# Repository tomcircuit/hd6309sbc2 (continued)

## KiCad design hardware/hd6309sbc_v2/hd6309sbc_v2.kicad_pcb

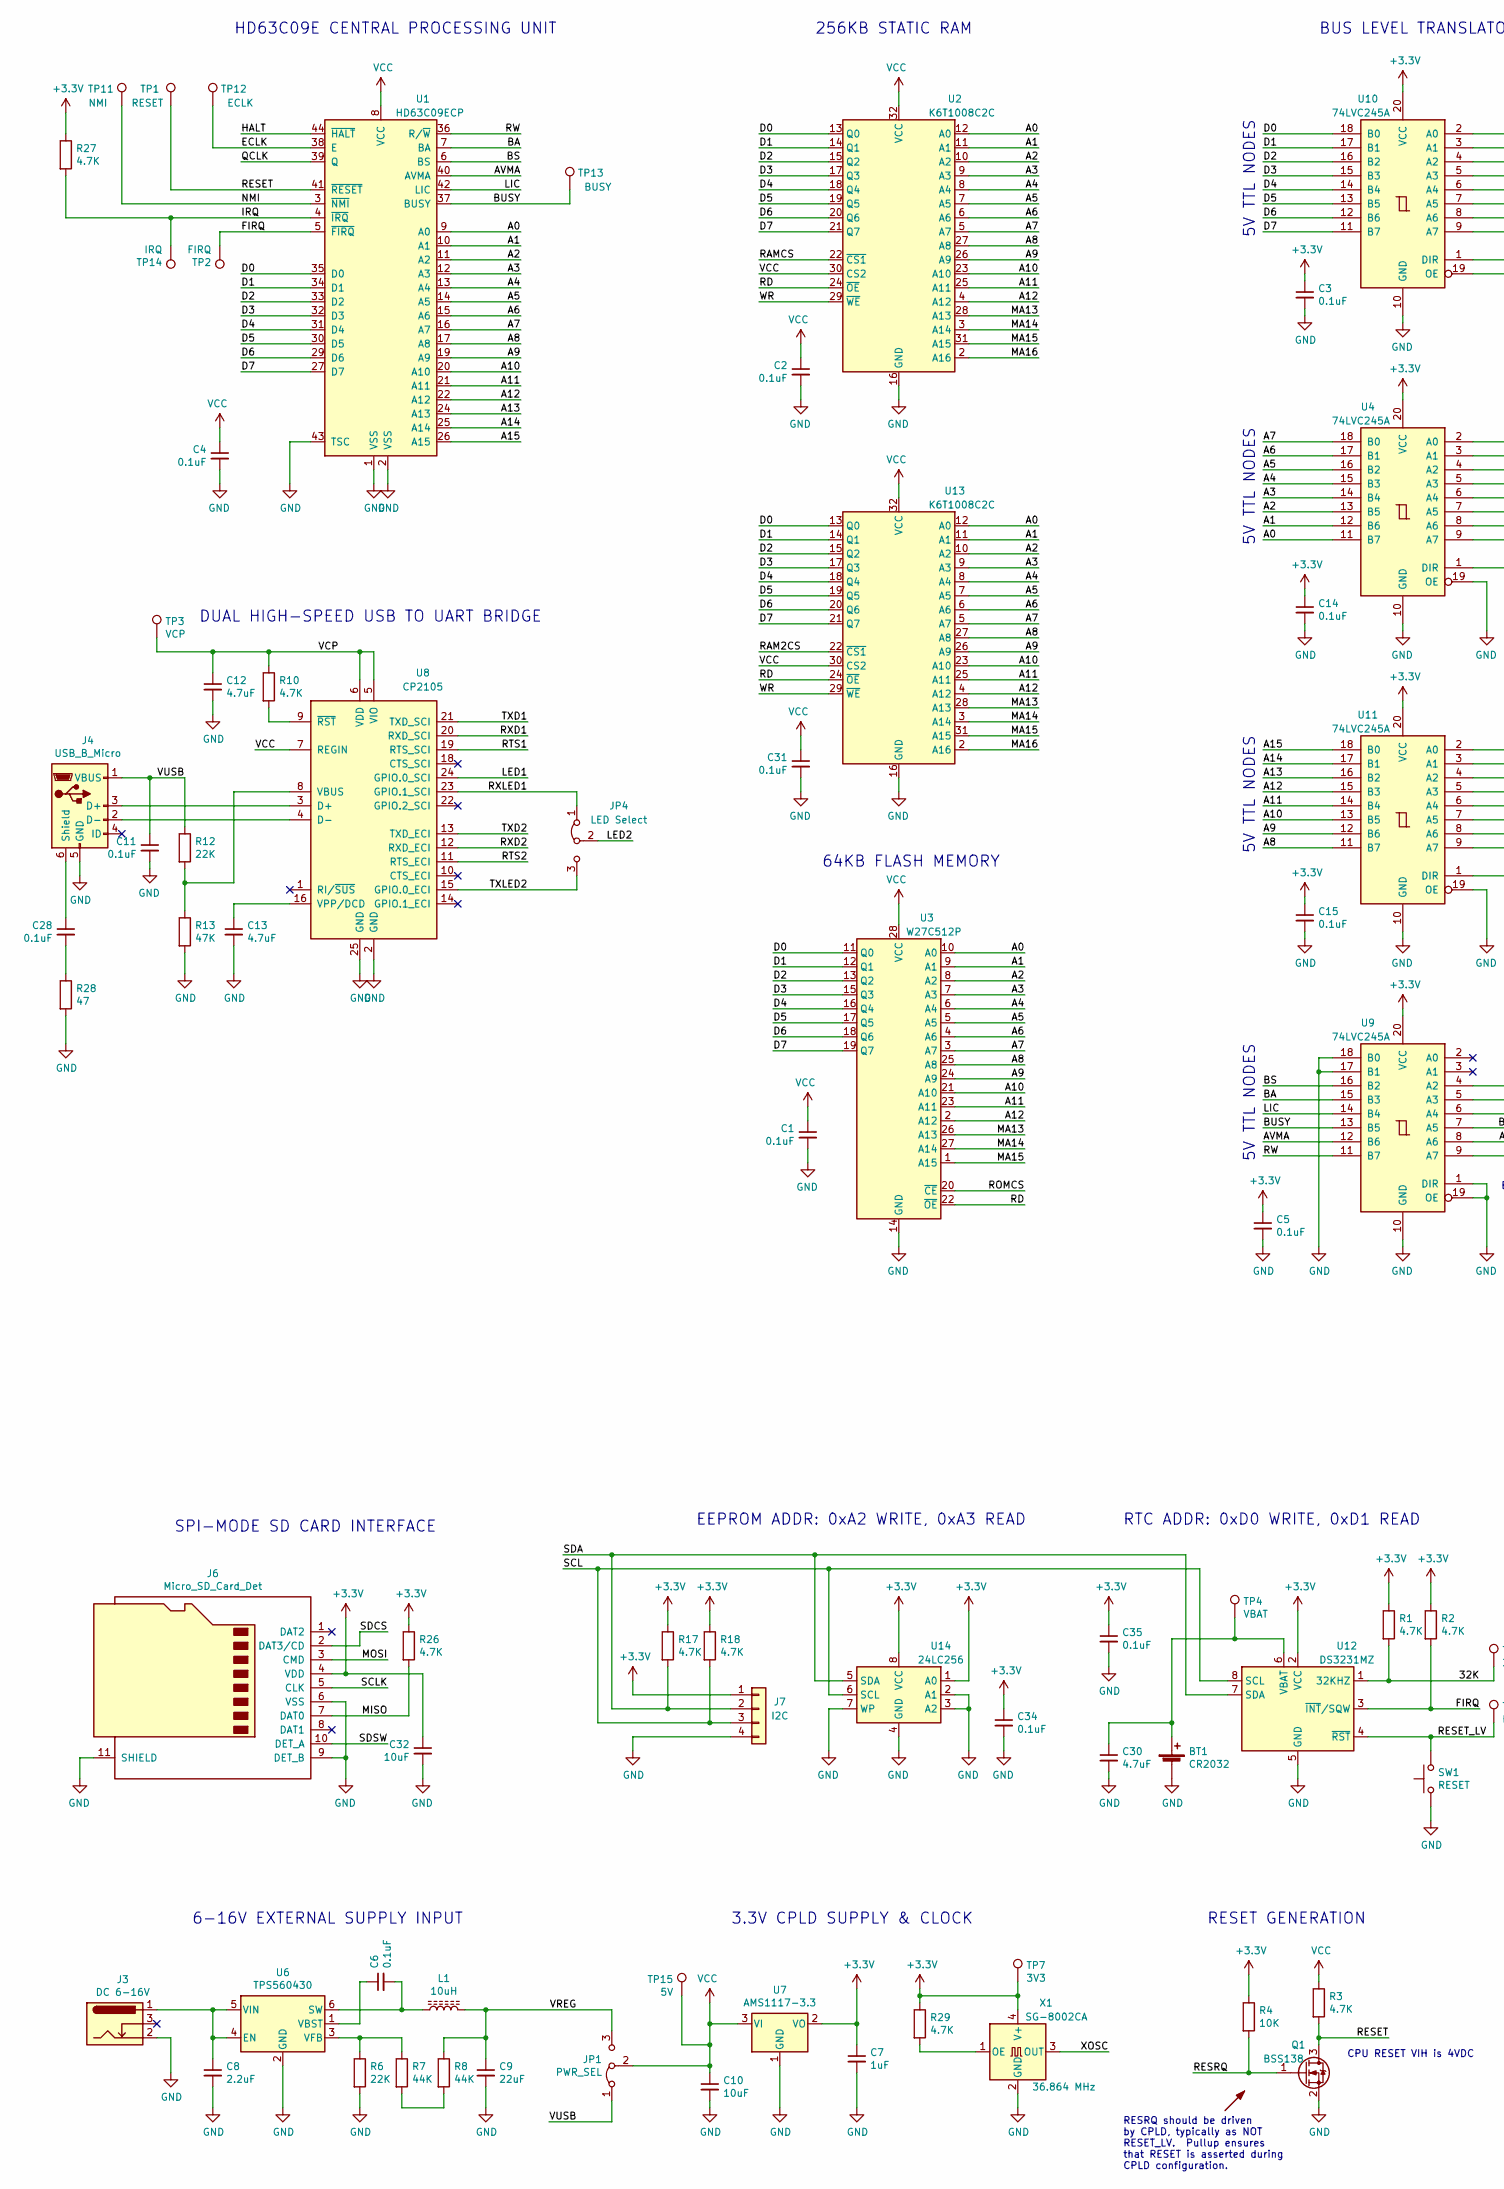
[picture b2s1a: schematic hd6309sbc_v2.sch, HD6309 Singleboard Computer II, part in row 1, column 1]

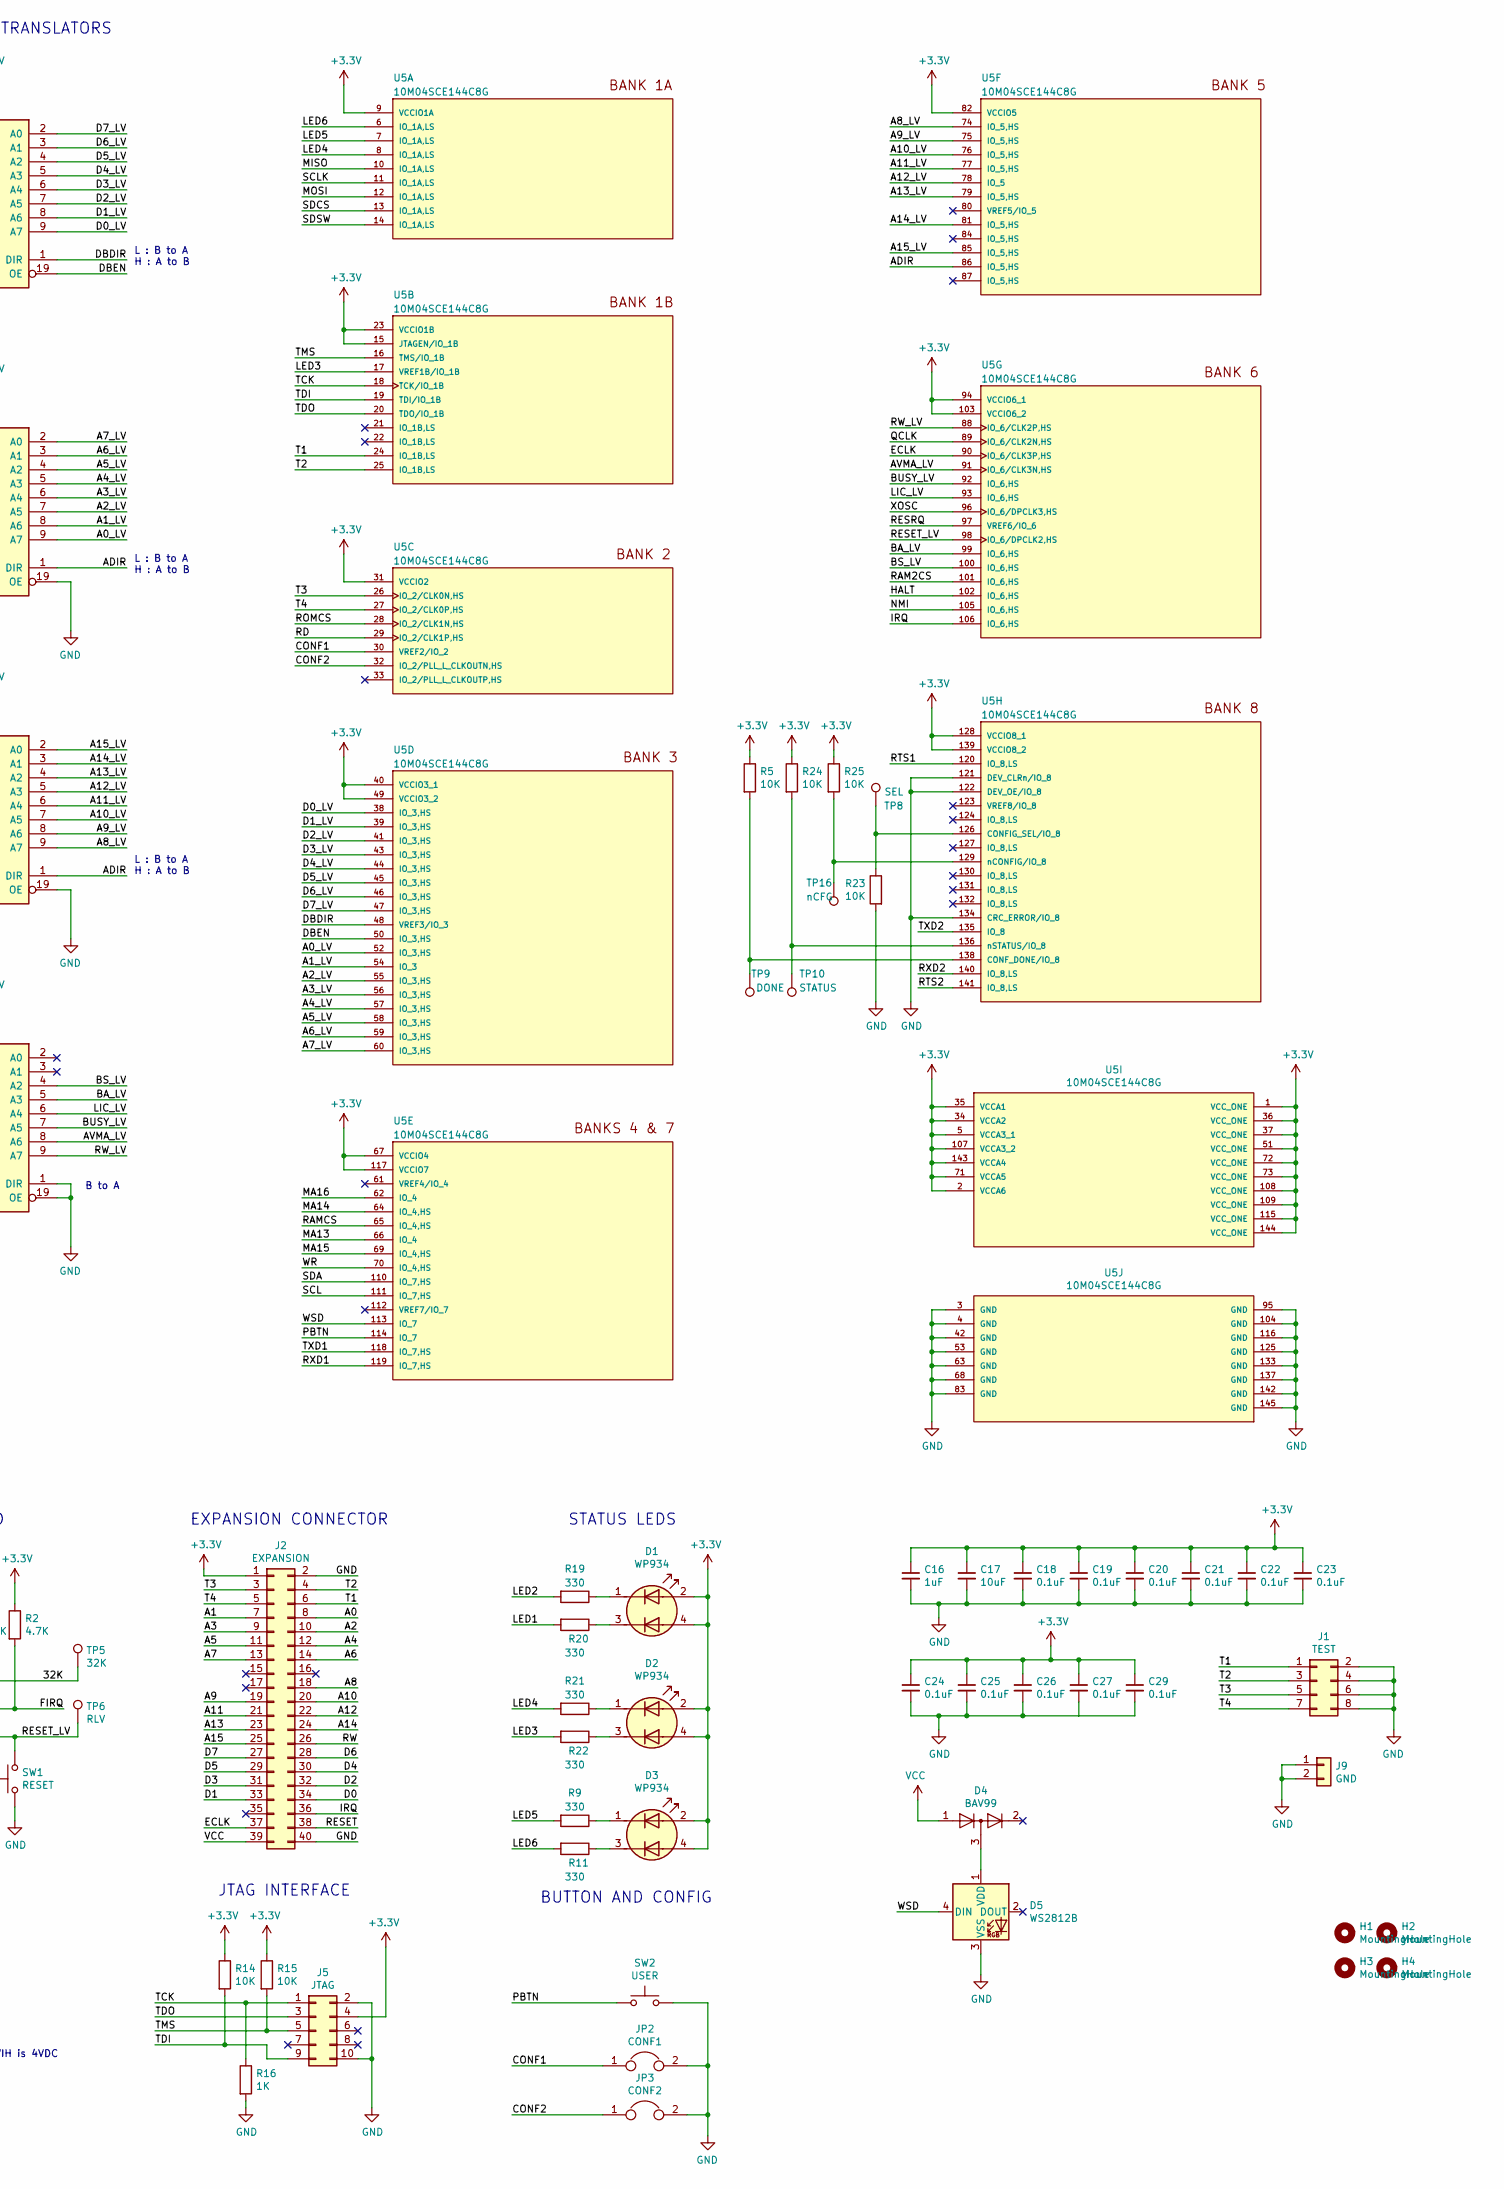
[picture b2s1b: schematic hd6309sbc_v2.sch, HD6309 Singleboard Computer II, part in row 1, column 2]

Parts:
BT1: CR2032; BatteryHolder_Keystone_1060_1x2032; MPN Keystone 1059
C1, C2, C3, C4, C5, C6, C11, C14, C15, C18, C19, C20, C21, C22, C23, C24, C25, C26, C27, C28, C29, C31, C34, C35: 0.1uF; C_0805_2012Metric_Pad1.15x1.40mm_HandSolder
C7, C16: 1uF; C_0805_2012Metric_Pad1.15x1.40mm_HandSolder
C8: 2.2uF; C_0805_2012Metric_Pad1.15x1.40mm_HandSolder
C9: 22uF; C_0805_2012Metric_Pad1.15x1.40mm_HandSolder
C10, C17, C32: 10uF; C_0805_2012Metric_Pad1.15x1.40mm_HandSolder
C12, C13, C30: 4.7uF; C_0805_2012Metric_Pad1.15x1.40mm_HandSolder
D1, D2, D3: WP934; 2GD
D4: BAV99; SOT-23
D5: WS2812B; LED_WS2812B_PLCC4_5.0x5.0mm_P3.2mm
H1, H2, H3, H4: MountingHole; MountingHole_4.3mm_M4_DIN965
J1: TEST; PinHeader_2x04_P2.54mm_Vertical
J2: EXPANSION; PinSocket_2x20_P2.54mm_Vertical
J3: DC 6-16V; BarrelJack_CUI_PJ-102AH_Horizontal
J4: USB_B_Micro; USB_Micro-B_Wuerth_629105150521
J5: JTAG; IDC-Header_2x05_P2.54mm_Vertical
J6: Micro_SD_Card_Det; microSD_HC_Hirose_DM3D-SF
J7: I2C; PinHeader_1x04_P2.54mm_Vertical
J9: GND; PinHeader_1x02_P2.54mm_Vertical
JP1: PWR_SEL; PinHeader_1x03_P2.54mm_Vertical
JP2: CONF1; PinHeader_1x02_P2.54mm_Vertical
JP3: CONF2; PinHeader_1x02_P2.54mm_Vertical
JP4: LED Select; PinHeader_1x03_P2.54mm_Vertical
L1: 10uH; L_Wuerth_MAPI-3020; MPN TDK VLS3012HBX-100M
Q1: BSS138; SOT-23
R1, R2, R3, R10, R17, R18, R26, R27, R29: 4.7K; R_0805_2012Metric_Pad1.15x1.40mm_HandSolder
R4, R5, R14, R15, R23, R24, R25: 10K; R_0805_2012Metric_Pad1.15x1.40mm_HandSolder
R6, R12: 22K; R_0805_2012Metric_Pad1.15x1.40mm_HandSolder
R7, R8: 44K; R_0805_2012Metric_Pad1.15x1.40mm_HandSolder
R9, R11, R19, R20, R21, R22: 330; R_0805_2012Metric_Pad1.15x1.40mm_HandSolder
R13: 47K; R_0805_2012Metric_Pad1.15x1.40mm_HandSolder
R16: 1K; R_0805_2012Metric_Pad1.15x1.40mm_HandSolder
R28: 47; R_0805_2012Metric_Pad1.15x1.40mm_HandSolder
SW1: RESET; SW_Tactile_SPST_Angled_PTS645Vx58-2LFS
SW2: USER; SW_Tactile_SPST_Angled_PTS645Vx58-2LFS
TP1: RESET; TestPoint_THTPad_2.0x2.0mm_Drill1.0mm
TP2: FIRQ; TestPoint_THTPad_2.0x2.0mm_Drill1.0mm
TP3: VCP; TestPoint_Pad_D1.5mm
TP4: VBAT; TestPoint_Pad_D1.5mm
TP5: 32K; TestPoint_Pad_D1.5mm
TP6: RLV; TestPoint_THTPad_2.0x2.0mm_Drill1.0mm
TP7: 3V3; TestPoint_THTPad_2.0x2.0mm_Drill1.0mm
TP8: SEL; TestPoint_Pad_D1.5mm
TP9: DONE; TestPoint_Pad_D1.5mm
TP10: STATUS; TestPoint_Pad_D1.5mm
TP11: NMI; TestPoint_THTPad_2.0x2.0mm_Drill1.0mm
TP12: ECLK; TestPoint_THTPad_2.0x2.0mm_Drill1.0mm
TP13: BUSY; TestPoint_THTPad_2.0x2.0mm_Drill1.0mm
TP14: IRQ; TestPoint_THTPad_2.0x2.0mm_Drill1.0mm
TP15: 5V; TestPoint_THTPad_2.0x2.0mm_Drill1.0mm
TP16: nCFG; TestPoint_Pad_D1.5mm
U1: HD63C09ECP; PLCC-44
U2, U13: K6T1008C2C; SSOP-32_11.305x20.495mm_P1.27mm
U3: W27C512P; DIP-28_W15.24mm
U4, U9, U10, U11: 74LVC245A; TSSOP-20_4.4x6.5mm_P0.65mm
U5: 10M04SCE144C8G; EQFP-144-1EP_20x20mm_P0.5mm_EP5x5mm
U6: TPS560430; SOT-23-6
U7: AMS1117-3.3; SOT-223-3_TabPin2
U8: CP2105; QFN-24-1EP_4x4mm_P0.5mm_EP2.6x2.6mm
U12: DS3231MZ; SOIC-8_3.9x4.9mm_P1.27mm
U14: 24LC256; SO-8_3.9x4.9mm_P1.27mm
X1: SG-8002CA; Oscillator_SMD_SeikoEpson_SG8002CA-4Pin_7.0x5.0mm

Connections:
+3V3: C3.1, C5.1, C7.1, C14.1, C15.1, C16.1, C17.1, C18.1, C19.1, C20.1, C21.1, C22.1, C23.1, C24.1, C25.1, C26.1, C27.1, C29.1, C32.1, C34.1, C35.1, D1.2 (K1), D1.4 (K2), D2.2 (K1), D2.4 (K2), D3.2 (K1), D3.4 (K2), J2.1, J5.4, J6.4 (VDD), J7.1, R1.1, R2.1, R4.1, R5.1, R14.1, R15.1, R17.1, R18.1, R24.1, R25.1, R26.1, R27.1, R29.1, TP7.1, U4.20 (VCC), U5.1 (VCC_ONE), U5.2 (VCCA6), U5.5 (VCCA3_1), U5.9 (VCCIO1A), U5.15 (JTAGEN/IO_1B), U5.23 (VCCIO1B), U5.31 (VCCIO2), U5.34 (VCCA2), U5.35 (VCCA1), U5.36 (VCC_ONE), U5.37 (VCC_ONE), U5.40 (VCCIO3_1), U5.49 (VCCIO3_2), U5.51 (VCC_ONE), U5.67 (VCCIO4), U5.71 (VCCA5), U5.72 (VCC_ONE), U5.73 (VCC_ONE), U5.82 (VCCIO5), U5.94 (VCCIO6_1), U5.103 (VCCIO6_2), U5.107 (VCCA3_2), U5.108 (VCC_ONE), U5.109 (VCC_ONE), U5.115 (VCC_ONE), U5.117 (VCCIO7), U5.128 (VCCIO8_1), U5.139 (VCCIO8_2), U5.143 (VCCA4), U5.144 (VCC_ONE), U7.2 (VO), U9.20 (VCC), U10.20 (VCC), U11.20 (VCC), U12.2 (VCC), U14.1 (A0), U14.8 (VCC), X1.4 (V+)
/32K: R1.2, TP5.1, U12.1 (32KHZ)
/A0: J2.8, U1.9 (A0), U2.12 (A0), U3.10 (A0), U4.11 (B7), U13.12 (A0)
/A0_LV: U4.9 (A7), U5.52 (IO_3,HS)
/A1: J2.7, U1.10 (A1), U2.11 (A1), U3.9 (A1), U4.12 (B6), U13.11 (A1)
/A1_LV: U4.8 (A6), U5.54 (IO_3)
/A2: J2.10, U1.11 (A2), U2.10 (A2), U3.8 (A2), U4.13 (B5), U13.10 (A2)
/A2_LV: U4.7 (A5), U5.55 (IO_3,HS)
/A3: J2.9, U1.12 (A3), U2.9 (A3), U3.7 (A3), U4.14 (B4), U13.9 (A3)
/A3_LV: U4.6 (A4), U5.56 (IO_3,HS)
/A4: J2.12, U1.13 (A4), U2.8 (A4), U3.6 (A4), U4.15 (B3), U13.8 (A4)
/A4_LV: U4.5 (A3), U5.57 (IO_3,HS)
/A5: J2.11, U1.14 (A5), U2.7 (A5), U3.5 (A5), U4.16 (B2), U13.7 (A5)
/A5_LV: U4.4 (A2), U5.58 (IO_3,HS)
/A6: J2.14, U1.15 (A6), U2.6 (A6), U3.4 (A6), U4.17 (B1), U13.6 (A6)
/A6_LV: U4.3 (A1), U5.59 (IO_3,HS)
/A7: J2.13, U1.16 (A7), U2.5 (A7), U3.3 (A7), U4.18 (B0), U13.5 (A7)
/A7_LV: U4.2 (A0), U5.60 (IO_3,HS)
/A8: J2.18, U1.17 (A8), U2.27 (A8), U3.25 (A8), U11.11 (B7), U13.27 (A8)
/A8_LV: U5.74 (IO_5,HS), U11.9 (A7)
/A9: J2.19, U1.19 (A9), U2.26 (A9), U3.24 (A9), U11.12 (B6), U13.26 (A9)
/A9_LV: U5.75 (IO_5,HS), U11.8 (A6)
/A10: J2.20, U1.20 (A10), U2.23 (A10), U3.21 (A10), U11.13 (B5), U13.23 (A10)
/A10_LV: U5.76 (IO_5,HS), U11.7 (A5)
/A11: J2.21, U1.21 (A11), U2.25 (A11), U3.23 (A11), U11.14 (B4), U13.25 (A11)
/A11_LV: U5.77 (IO_5,HS), U11.6 (A4)
/A12: J2.22, U1.22 (A12), U2.4 (A12), U3.2 (A12), U11.15 (B3), U13.4 (A12)
/A12_LV: U5.78 (IO_5), U11.5 (A3)
/A13: J2.23, U1.24 (A13), U11.16 (B2)
/A13_LV: U5.79 (IO_5,HS), U11.4 (A2)
/A14: J2.24, U1.25 (A14), U11.17 (B1)
/A14_LV: U5.81 (IO_5,HS), U11.3 (A1)
/A15: J2.25, U1.26 (A15), U11.18 (B0)
/A15_LV: U5.85 (IO_5,HS), U11.2 (A0)
/ADIR: U4.1 (DIR), U5.86 (IO_5,HS), U11.1 (DIR)
/AVMA: U1.40 (AVMA), U9.12 (B6)
/AVMA_LV: U5.91 (IO_6/CLK3N,HS), U9.8 (A6)
/BA: U1.7 (BA), U9.15 (B3)
/BA_LV: U5.99 (IO_6,HS), U9.5 (A3)
/BS: U1.6 (BS), U9.16 (B2)
/BS_LV: U5.100 (IO_6,HS), U9.4 (A2)
/BUSY: TP13.1, U1.37 (BUSY), U9.13 (B5)
/BUSY_LV: U5.92 (IO_6,HS), U9.7 (A5)
/CONF1: JP2.1, U5.30 (VREF2/IO_2)
/CONF2: JP3.1, U5.32 (IO_2/PLL_L_CLKOUTN,HS)
/D0: J2.34, U1.35 (D0), U2.13 (Q0), U3.11 (Q0), U10.18 (B0), U13.13 (Q0)
/D0_LV: U5.38 (IO_3,HS), U10.9 (A7)
/D1: J2.33, U1.34 (D1), U2.14 (Q1), U3.12 (Q1), U10.17 (B1), U13.14 (Q1)
/D1_LV: U5.39 (IO_3,HS), U10.8 (A6)
/D2: J2.32, U1.33 (D2), U2.15 (Q2), U3.13 (Q2), U10.16 (B2), U13.15 (Q2)
/D2_LV: U5.41 (IO_3,HS), U10.7 (A5)
/D3: J2.31, U1.32 (D3), U2.17 (Q3), U3.15 (Q3), U10.15 (B3), U13.17 (Q3)
/D3_LV: U5.43 (IO_3,HS), U10.6 (A4)
/D4: J2.30, U1.31 (D4), U2.18 (Q4), U3.16 (Q4), U10.14 (B4), U13.18 (Q4)
/D4_LV: U5.44 (IO_3,HS), U10.5 (A3)
/D5: J2.29, U1.30 (D5), U2.19 (Q5), U3.17 (Q5), U10.13 (B5), U13.19 (Q5)
/D5_LV: U5.45 (IO_3,HS), U10.4 (A2)
/D6: J2.28, U1.29 (D6), U2.20 (Q6), U3.18 (Q6), U10.12 (B6), U13.20 (Q6)
/D6_LV: U5.46 (IO_3,HS), U10.3 (A1)
/D7: J2.27, U1.27 (D7), U2.21 (Q7), U3.19 (Q7), U10.11 (B7), U13.21 (Q7)
/D7_LV: U5.47 (IO_3,HS), U10.2 (A0)
/DBDIR: U5.48 (VREF3/IO_3), U10.1 (DIR)
/DBEN: U5.50 (IO_3,HS), U10.19 (OE)
/ECLK: J2.37, TP12.1, U1.38 (E), U5.90 (IO_6/CLK3P,HS)
/FIRQ: R2.2, TP2.1, U1.5 (~FIRQ), U12.3 (~INT~/SQW)
/HALT: U1.44 (~HALT), U5.102 (IO_6,HS)
/IRQ: J2.36, R27.2, TP14.1, U1.4 (~IRQ), U5.106 (IO_6,HS)
/LED1: R20.2, U8.24 (GPIO.0_SCI)
/LED2: JP4.2 (C), R19.2
/LED3: R22.2, U5.17 (VREF1B/IO_1B)
/LED4: R21.2, U5.8 (IO_1A,LS)
/LED5: R9.2, U5.7 (IO_1A,LS)
/LED6: R11.2, U5.6 (IO_1A,LS)
/LIC: U1.42 (LIC), U9.14 (B4)
/LIC_LV: U5.93 (IO_6,HS), U9.6 (A4)
/MA13: U2.28 (A13), U3.26 (A13), U5.66 (IO_4), U13.28 (A13)
/MA14: U2.3 (A14), U3.27 (A14), U5.64 (IO_4,HS), U13.3 (A14)
/MA15: U2.31 (A15), U3.1 (A15), U5.69 (IO_4,HS), U13.31 (A15)
/MA16: U2.2 (A16), U5.62 (IO_4), U13.2 (A16)
/MISO: J6.7 (DAT0), R26.2, U5.10 (IO_1A,LS)
/MOSI: J6.3 (CMD), U5.12 (IO_1A,LS)
/NMI: TP11.1, U1.3 (~NMI), U5.105 (IO_6,HS)
/PBTN: SW2.1, U5.114 (IO_7)
/QCLK: U1.39 (Q), U5.89 (IO_6/CLK2N,HS)
/RAM2CS: U5.101 (IO_6,HS), U13.22 (~CS1)
/RAMCS: U2.22 (~CS1), U5.65 (IO_4,HS)
/RD: U2.24 (~OE), U3.22 (~OE), U5.29 (IO_2/CLK1P,HS), U13.24 (~OE)
/RESET: J2.38, Q1.3 (D), R3.2, TP1.1, U1.41 (~RESET)
/RESET_LV: SW1.2, TP6.1, U5.98 (IO_6/DPCLK2,HS), U12.4 (~RST)
/RESRQ: Q1.1 (G), R4.2, U5.97 (VREF6/IO_6)
/ROMCS: U3.20 (~CE), U5.28 (IO_2/CLK1N,HS)
/RTS1: U5.120 (IO_8,LS), U8.19 (RTS_SCI)
/RTS2: U5.141 (IO_8,LS), U8.11 (RTS_ECI)
/RW: J2.26, U1.36 (R/~W), U9.11 (B7)
/RW_LV: U5.88 (IO_6/CLK2P,HS), U9.9 (A7)
/RXD1: U5.119 (IO_7,HS), U8.20 (RXD_SCI)
/RXD2: U5.140 (IO_8,LS), U8.12 (RXD_ECI)
/RXLED1: JP4.1 (A), U8.23 (GPIO.1_SCI)
/SCL: J7.3, R18.2, U5.111 (IO_7,HS), U12.8 (SCL), U14.6 (SCL)
/SCLK: J6.5 (CLK), U5.11 (IO_1A,LS)
/SDA: J7.2, R17.2, U5.110 (IO_7,HS), U12.7 (SDA), U14.5 (SDA)
/SDCS: J6.2 (DAT3/CD), U5.13 (IO_1A,LS)
/SDSW: J6.10 (DET_A), U5.14 (IO_1A,LS)
/T1: J1.1, J2.6, U5.24 (IO_1B,LS)
/T2: J1.3, J2.4, U5.25 (IO_1B,LS)
/T3: J1.5, J2.3, U5.26 (IO_2/CLK0N,HS)
/T4: J1.7, J2.5, U5.27 (IO_2/CLK0P,HS)
/TCK: J5.1, R16.1, U5.18 (TCK/IO_1B)
/TDI: J5.9, R14.2, U5.19 (TDI/IO_1B)
/TDO: J5.3, U5.20 (TDO/IO_1B)
/TMS: J5.5, R15.2, U5.16 (TMS/IO_1B)
/TXD1: U5.118 (IO_7,HS), U8.21 (TXD_SCI)
/TXD2: U5.135 (IO_8), U8.13 (TXD_ECI)
/TXLED2: JP4.3 (B), U8.15 (GPIO.0_ECI)
/VCP: C12.1, R10.1, TP3.1, U8.5 (VIO), U8.6 (VDD)
/VREG: C9.1, JP1.3 (B), L1.2, R8.1
/VUSB: C11.1, J4.1 (VBUS), JP1.1 (A), R12.1
/WR: U2.29 (~WE), U5.70 (IO_4,HS), U13.29 (~WE)
/WSD: D5.4 (DIN), U5.113 (IO_7)
/XOSC: U5.96 (IO_6/DPCLK3,HS), X1.3 (OUT)
GND: BT1.2 (-), C1.2, C2.2, C3.2, C4.2, C5.2, C7.2, C8.2, C9.2, C10.2, C11.2, C12.2, C13.2, C14.2, C15.2, C16.2, C17.2, C18.2, C19.2, C20.2, C21.2, C22.2, C23.2, C24.2, C25.2, C26.2, C27.2, C29.2, C30.2, C31.2, C32.2, C34.2, C35.2, D5.3 (VSS), J1.2, J1.4, J1.6, J1.8, J2.2, J2.40, J3.2, J4.5 (GND), J5.2, J5.10, J6.6 (VSS), J6.9 (DET_B), J6.11 (SHIELD), J7.4, J9.1, J9.2, JP2.2, JP3.2, Q1.2 (S), R6.2, R13.2, R16.2, R23.2, R28.2, SW1.1, SW2.2, U1.1 (VSS), U1.2 (VSS), U1.43 (TSC), U2.16 (GND), U3.14 (GND), U4.10 (GND), U4.19 (OE), U5.3 (GND), U5.4 (GND), U5.42 (GND), U5.53 (GND), U5.63 (GND), U5.68 (GND), U5.83 (GND), U5.95 (GND), U5.104 (GND), U5.116 (GND), U5.121 (DEV_CLRn/IO_8), U5.122 (DEV_OE/IO_8), U5.125 (GND), U5.133 (GND), U5.134 (CRC_ERROR/IO_8), U5.137 (GND), U5.142 (GND), U5.145 (GND), U6.2 (GND), U7.1 (GND), U8.2 (GND), U8.25 (GND), U9.1 (DIR), U9.10 (GND), U9.17 (B1), U9.18 (B0), U9.19 (OE), U10.10 (GND), U11.10 (GND), U11.19 (OE), U12.5 (GND), U13.16 (GND), U14.2 (A1), U14.3 (A2), U14.4 (GND), U14.7 (WP), X1.2 (GND); also elsewhere on the board
unnamed: BT1.1 (+), C30.1, TP4.1, U12.6 (VBAT)
unnamed: C6.1, U6.1 (VBST)
unnamed: C6.2, L1.1, U6.6 (SW)
unnamed: C8.1, J3.1, U6.4 (EN), U6.5 (VIN)
unnamed: C13.1, U8.16 (VPP/DCD)
unnamed 126: C28.1, J4.6 (Shield); also elsewhere on the board
unnamed: C28.2, R28.1
unnamed: D1.1 (A1), R19.1
unnamed: D1.3 (A2), R20.1
unnamed: D2.1 (A1), R21.1
unnamed: D2.3 (A2), R22.1
unnamed: D3.1 (A1), R9.1
unnamed: D3.3 (A2), R11.1
unnamed: D4.3 (K), D5.1 (VDD)
unnamed: J4.2 (D-), U8.4 (D-)
unnamed: J4.3 (D+), U8.3 (D+)
unnamed: R5.2, TP9.1, U5.138 (CONF_DONE/IO_8)
unnamed: R6.1, R7.1, U6.3 (VFB)
unnamed: R7.2, R8.2
unnamed: R10.2, U8.9 (~RST)
unnamed: R12.2, R13.1, U8.8 (VBUS)
unnamed: R23.1, TP8.1, U5.126 (CONFIG_SEL/IO_8)
unnamed: R24.2, TP10.1, U5.136 (nSTATUS/IO_8)
unnamed: R25.2, TP16.1, U5.129 (nCONFIG/IO_8)
unnamed: R29.2, X1.1 (OE)
VCC: C1.1, C2.1, C4.1, C10.1, C31.1, D4.1 (K), J2.39, JP1.2 (C), R3.1, TP15.1, U1.8 (VCC), U2.30 (CS2), U2.32 (VCC), U3.28 (VCC), U7.3 (VI), U8.7 (REGIN), U13.30 (CS2), U13.32 (VCC)

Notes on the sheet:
6-16V EXTERNAL SUPPLY INPUT
3.3V CPLD SUPPLY & CLOCK
DUAL HIGH-SPEED USB TO UART BRIDGE
RTC ADDR: 0xD0 WRITE, 0xD1 READ
EEPROM ADDR: 0xA2 WRITE, 0xA3 READ
SPI-MODE SD CARD INTERFACE
5V TTL NODES
BUTTON AND CONFIG
JTAG INTERFACE
STATUS LEDS
RESRQ should be driven by CPLD, typically as NOT RESET_LV. Pullup ensures that RESET is asserted during CPLD configuration.
HD63C09E CENTRAL PROCESSING UNIT
256KB STATIC RAM
64KB FLASH MEMORY
BUS LEVEL TRANSLATORS
CPU RESET VIH is 4VDC
RESET GENERATION
EXPANSION CONNECTOR
B to A
L : B to A H : A to B

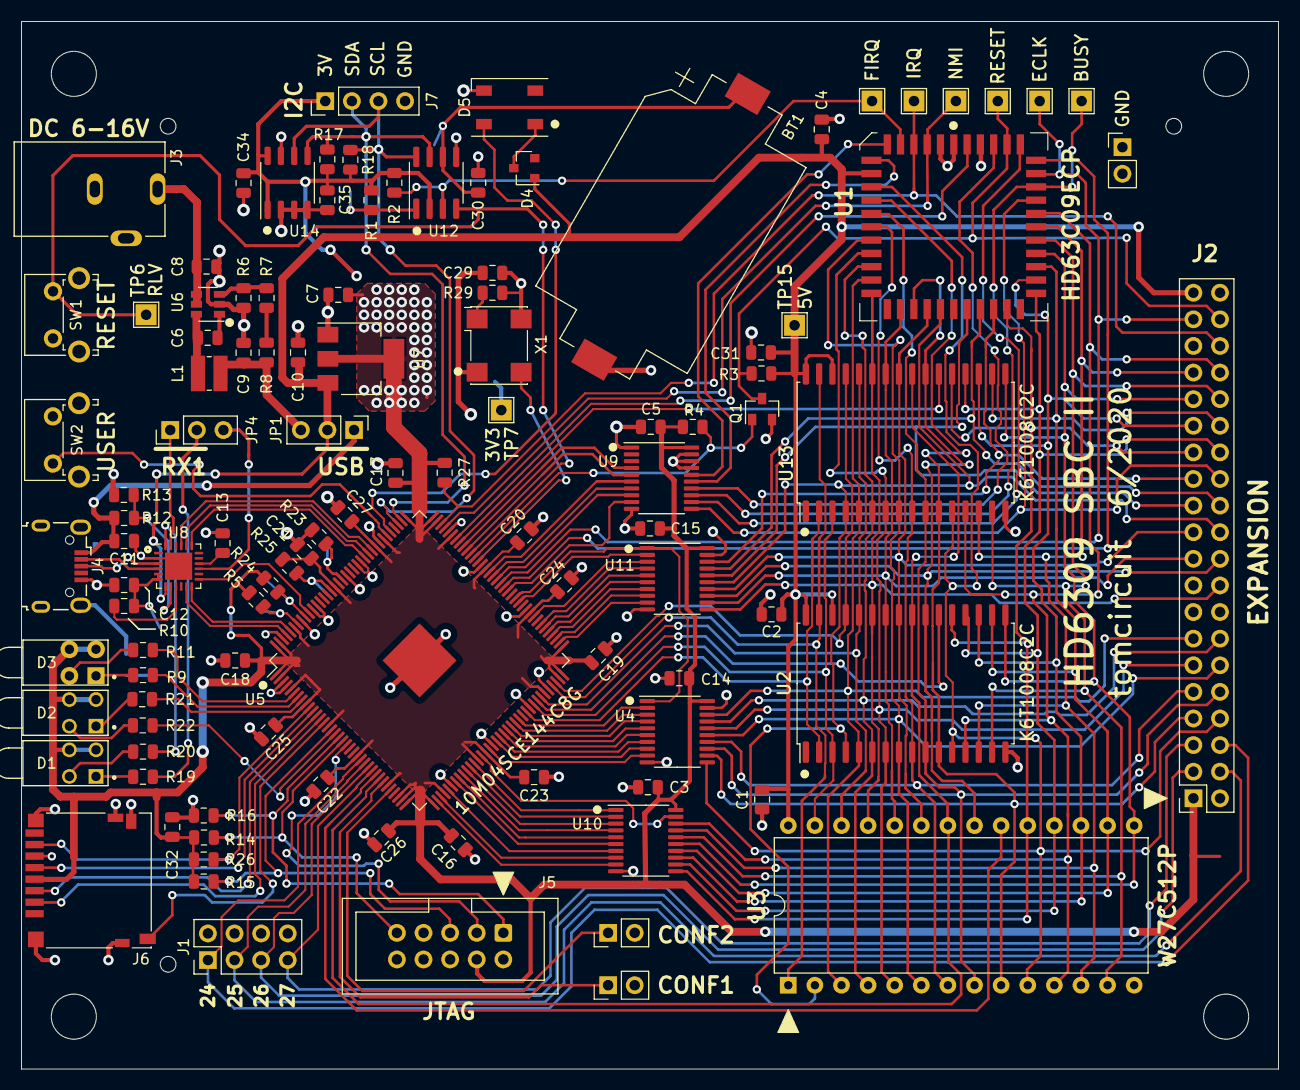
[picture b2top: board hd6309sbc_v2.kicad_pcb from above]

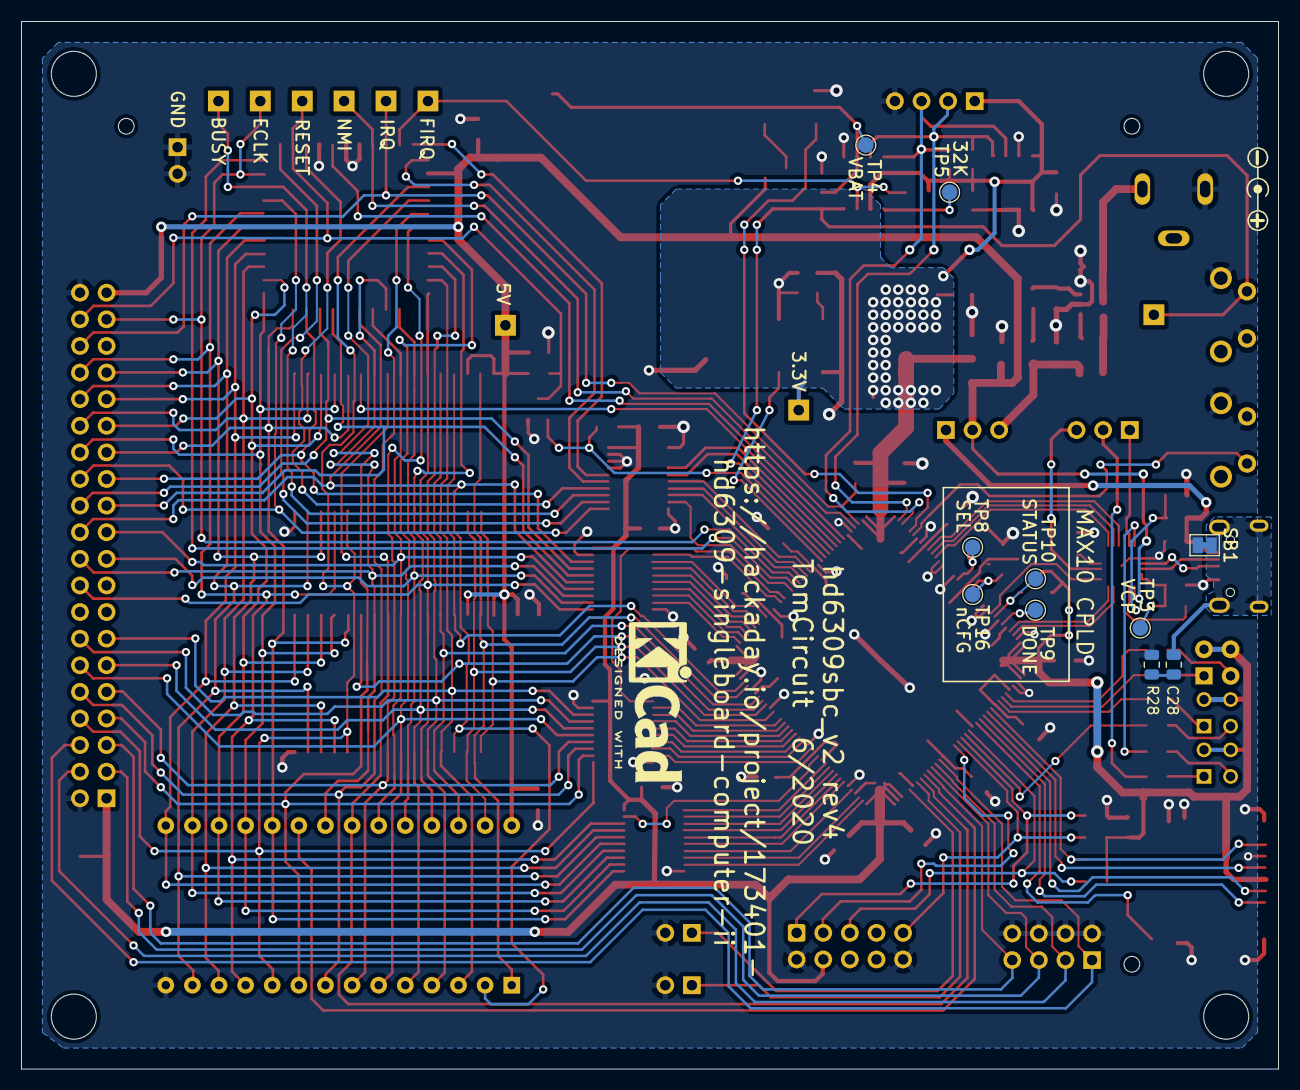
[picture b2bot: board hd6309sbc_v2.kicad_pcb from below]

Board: 2 copper layers, 120.0 x 100.0 mm, 124 parts (10 on the bottom side), 147 nets.

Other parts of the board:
SB1: SolderJumper-2_P1.3mm_Bridged_Pad1.0x1.5mm
STENCIL1, STENCIL1#2, STENCIL1#3: MountingHole_2.1mm

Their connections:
GND: SB1.2; also elsewhere on the board
unnamed 126: SB1.1; also elsewhere on the board

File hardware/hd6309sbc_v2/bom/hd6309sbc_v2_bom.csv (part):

Source:,C:\Users\lemenset\Documents\Projects\Personal\6309 SBC II\hardware\hd6309sbc_v2\hd6309sbc_v2.sch,,,,,,
Date:,7/9/2020 15:16,,,,,,
Tool:,Eeschema (5.1.6)-1,,,,,,
Generator:,C:\Program Files\KiCad\bin\scripting\plugins/bom_csv_grouped_by_value_with_fp.py,,,,,,
Component Count:,120,,,,,,
Ref,Qnty,Value,Cmp name,Footprint,Description,Vendor,Distributor & P/N
"BT1, ",1,CR2032,Battery_Cell,Battery:BatteryHolder_Keystone_1060_1x2032,Single-cell battery,Keystone,Mouser 534-1060TR 
"C1, C2, C3, C4, C5, C6, C11, C14, C15, C18, C19, C20, C21, C22, C23, C24, C25, C26, C27, C28, C29, C31, C34, C35, ",24,0.1uF,C_Small,Capacitor_SMD:C_0805_2012Metric_Pad1.15x1.40mm_HandSolder,"Unpolarized capacitor, small symbol",,Mouser 581-08055C104KAT4A
"C7, C16, ",2,1uF,C_Small,Capacitor_SMD:C_0805_2012Metric_Pad1.15x1.40mm_HandSolder,"Unpolarized capacitor, small symbol",,Mouser 963-LMK212B7105KG-T
"C8, ",1,2.2uF,C_Small,Capacitor_SMD:C_0805_2012Metric_Pad1.15x1.40mm_HandSolder,"Unpolarized capacitor, small symbol",,Mouser 963-UMK212BB7225MG-T
"C9, ",1,22uF,C_Small,Capacitor_SMD:C_0805_2012Metric_Pad1.15x1.40mm_HandSolder,"Unpolarized capacitor, small symbol",,Mouser 81-GRM21BR61H475KE1L
"C10, C17, C32, ",3,10uF,C_Small,Capacitor_SMD:C_0805_2012Metric_Pad1.15x1.40mm_HandSolder,"Unpolarized capacitor, small symbol",,Mouser 81-GRM21BR61A226ME1L
"C12, C13, C30, ",3,4.7uF,C_Small,Capacitor_SMD:C_0805_2012Metric_Pad1.15x1.40mm_HandSolder,"Unpolarized capacitor, small symbol",,Mouser 810-C2012X7R1A106KAE
"D1, D2, D3, ",3,WP934,LED_Dual_CACA,LED_WP934MD:2GD,"Dual LED, cathodes on pins 1 and 3",,on stock
"D4, ",1,BAV99,BAV99,Package_TO_SOT_SMD:SOT-23,"BAV99 High-speed switching diodes, SOT-23",,on stock
"D5, ",1,WS2812B,WS2812B,LED_SMD:LED_WS2812B_PLCC4_5.0x5.0mm_P3.2mm,RGB LED with integrated controller,,on stock
"H1, H2, H3, H4, ",4,MountingHole,MountingHole,MountingHole:MountingHole_4.3mm_M4_DIN965,Mounting Hole without connection,,on stock
"J1, ",1,TEST,Conn_02x04_Odd_Even,Connector_PinHeader_2.54mm:PinHeader_2x04_P2.54mm_Vertical,"Generic connector, double row, 02x04, odd/even pin numbering scheme (row 1 odd numbers, row 2 even numbers), script generated (kicad-library-utils/schlib/autogen/connector/)",,on stock
"J2, ",1,EXPANSION,Conn_02x20_Odd_Even,Connector_PinSocket_2.54mm:PinSocket_2x20_P2.54mm_Vertical,"Generic connector, double row, 02x20, odd/even pin numbering scheme (row 1 odd numbers, row 2 even numbers), script generated (kicad-library-utils/schlib/autogen/connector/)",,Mouser 855-M20-7832046 
"J3, ",1,DC 6-16V,Barrel_Jack_Switch,Connector_BarrelJack:BarrelJack_CUI_PJ-102AH_Horizontal,DC Barrel Jack with an internal switch,,Mouser 490-PJ-102AH 
"J4, ",1,USB_B_Micro,USB_B_Micro,Connector_USB:USB_Micro-B_Wuerth_629105150521,USB Micro Type B connector,,Mouser 710-629105150521 
"J5, ",1,JTAG,Conn_02x05_Odd_Even,Connector_IDC:IDC-Header_2x05_P2.54mm_Vertical,"Generic connector, double row, 02x05, odd/even pin numbering scheme (row 1 odd numbers, row 2 even numbers), script generated (kicad-library-utils/schlib/autogen/connector/)",,on stock
"J6, ",1,Micro_SD_Card_Det,Micro_SD_Card_Det,Connector_Card:microSD_HC_Hirose_DM3D-SF,Micro SD Card Socket with card detection pins,,Mouser 798-DM3D-SF
"J7, ",1,I2C,Conn_01x04,Connector_PinHeader_2.54mm:PinHeader_1x04_P2.54mm_Vertical,"Generic connector, single row, 01x04, script generated (kicad-library-utils/schlib/autogen/connector/)",,on stock
"J9, ",1,GND,Conn_01x02,Connector_PinHeader_2.54mm:PinHeader_1x02_P2.54mm_Vertical,"Generic connector, single row, 01x02, script generated (kicad-library-utils/schlib/autogen/connector/)",,on stock
"JP1, ",1,PWR_SEL,Jumper_3_Bridged12,Connector_PinHeader_2.54mm:PinHeader_1x03_P2.54mm_Vertical,"Jumper, 3-pole, pins 1+2 closed/bridged",,on stock
"JP2, ",1,CONF1,Jumper,Connector_PinHeader_2.54mm:PinHeader_1x02_P2.54mm_Vertical,"Jumper, normally closed",,on stock
"JP3, ",1,CONF2,Jumper,Connector_PinHeader_2.54mm:PinHeader_1x02_P2.54mm_Vertical,"Jumper, normally closed",,on stock
"JP4, ",1,LED Select,Jumper_3_Bridged12,Connector_PinHeader_2.54mm:PinHeader_1x03_P2.54mm_Vertical,"Jumper, 3-pole, pins 1+2 closed/bridged",,on stock
"L1, ",1,10uH,L_Core_Ferrite,Inductor_SMD:L_Wuerth_MAPI-3020,Inductor with ferrite core,,Mouser 810-VLS3012HBX-100M
"Q1, ",1,BSS138,BSS138,Package_TO_SOT_SMD:SOT-23,"50V Vds, 0.22A Id, N-Channel MOSFET, SOT-23",,on stock
"R1, R2, R3, R10, R17, R18, R26, R27, R29, ",9,4.7K,R,Resistor_SMD:R_0805_2012Metric_Pad1.15x1.40mm_HandSolder,Resistor,,on stock
"R4, R5, R14, R15, R23, R24, R25, ",7,10K,R,Resistor_SMD:R_0805_2012Metric_Pad1.15x1.40mm_HandSolder,Resistor,,on stock
"R6, R12, ",2,22K,R,Resistor_SMD:R_0805_2012Metric_Pad1.15x1.40mm_HandSolder,Resistor,,on stock
"R7, R8, ",2,44K,R,Resistor_SMD:R_0805_2012Metric_Pad1.15x1.40mm_HandSolder,Resistor,,Mouser 71-CRCW0805-44.2K-E3 
"R9, R11, R19, R20, R21, R22, ",6,330,R,Resistor_SMD:R_0805_2012Metric_Pad1.15x1.40mm_HandSolder,Resistor,,on stock
"R13, ",1,47K,R,Resistor_SMD:R_0805_2012Metric_Pad1.15x1.40mm_HandSolder,Resistor,,on stock
"R16, ",1,1K,R,Resistor_SMD:R_0805_2012Metric_Pad1.15x1.40mm_HandSolder,Resistor,,on stock
"R28, ",1,47,R,Resistor_SMD:R_0805_2012Metric_Pad1.15x1.40mm_HandSolder,Resistor,,on stock
"SW1, ",1,RESET,SW_Push,Button_Switch_THT:SW_Tactile_SPST_Angled_PTS645Vx58-2LFS,"Push button switch, generic, two pins",,on stock
"SW2, ",1,USER,SW_Push,Button_Switch_THT:SW_Tactile_SPST_Angled_PTS645Vx58-2LFS,"Push button switch, generic, two pins",,on stock
"TP1, ",1,RESET,TestPoint,TestPoint:TestPoint_THTPad_2.0x2.0mm_Drill1.0mm,test point,,
"TP2, ",1,FIRQ,TestPoint,TestPoint:TestPoint_THTPad_2.0x2.0mm_Drill1.0mm,test point,,
"TP3, ",1,VCP,TestPoint,TestPoint:TestPoint_Pad_D1.5mm,test point,,
"TP4, ",1,VBAT,TestPoint,TestPoint:TestPoint_Pad_D1.5mm,test point,,
"TP5, ",1,32K,TestPoint,TestPoint:TestPoint_Pad_D1.5mm,test point,,
"TP6, ",1,RLV,TestPoint,TestPoint:TestPoint_THTPad_2.0x2.0mm_Drill1.0mm,test point,,
"TP7, ",1,3V3,TestPoint,TestPoint:TestPoint_THTPad_2.0x2.0mm_Drill1.0mm,test point,,
"TP8, ",1,SEL,TestPoint,TestPoint:TestPoint_Pad_D1.5mm,test point,,
"TP9, ",1,DONE,TestPoint,TestPoint:TestPoint_Pad_D1.5mm,test point,,
"TP10, ",1,STATUS,TestPoint,TestPoint:TestPoint_Pad_D1.5mm,test point,,
"TP11, ",1,NMI,TestPoint,TestPoint:TestPoint_THTPad_2.0x2.0mm_Drill1.0mm,test point,,
"TP12, ",1,ECLK,TestPoint,TestPoint:TestPoint_THTPad_2.0x2.0mm_Drill1.0mm,test point,,
"TP13, ",1,BUSY,TestPoint,TestPoint:TestPoint_THTPad_2.0x2.0mm_Drill1.0mm,test point,,
"TP14, ",1,IRQ,TestPoint,TestPoint:TestPoint_THTPad_2.0x2.0mm_Drill1.0mm,test point,,
"TP15, ",1,5V,TestPoint,TestPoint:TestPoint_THTPad_2.0x2.0mm_Drill1.0mm,test point,,
"TP16, ",1,nCFG,TestPoint,TestPoint:TestPoint_Pad_D1.5mm,test point,,
"U1, ",1,HD63C09ECP,HD63C09ECP,Package_LCC:PLCC-44,"8-Bit Microprocessing unit 3MHz, PLCC44",,on stock
"U2, U13, ",2,K6T1008C2C,K6T1008C2C-GL70,Package_SO:SSOP-32_11.305x20.495mm_P1.27mm,"128K x 8 High-Speed CMOS Static RAM, 70ns, DIP-32/SOP-32",,on stock
"U3, ",1,W27C512P,W27C512,Package_DIP:DIP-28_W15.24mm,"FLASH 512 KiBit, DIP-28",,on stock
"U4, U9, U10, U11, ",4,74LVC245A,74LVC245A,Package_SO:TSSOP-20_4.4x6.5mm_P0.65mm,"Octal BUS Transceivers, Low-Voltage CMOS, 5V Tolerant, 3-State outputs",,Mouser 595-SN74LVC245APWR
"U5, ",1,10M04SCE144C8G,10M04SCE144C8G,Package_QFP:EQFP-144-1EP_20x20mm_P0.5mm_EP5x5mm,,,Mouser 989-10M04SCE144C8G 
"U6, ",1,TPS560430,TPS560430,Package_TO_SOT_SMD:SOT-23-6,"0.6A Synchronous Step-Down Voltage Regulator, Adjustable Output Voltage, 4-36V Input Voltage, SOT-23-6",,Mouser 595-TPS560430YFDBVR
"U7, ",1,AMS1117-3.3,AMS1117-3.3,Package_TO_SOT_SMD:SOT-223-3_TabPin2,"1A Low Dropout regulator, positive, 3.3V fixed output, SOT-223",,Mouser 595-TLV1117-33IDCYR
"U8, ",1,CP2105,CP2105,Package_DFN_QFN:QFN-24-1EP_4x4mm_P0.5mm_EP2.6x2.6mm,"USB to dual UART master bridge, QFN-24",,Mouser 634-CP2105-F01-GMR
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
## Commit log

2020-07-10 Initial commit of HD6309 SBC II
    KiCAD database, PDF schematic, PDF PCB plots, CSV BOM, readme, license files.
2020-07-10 removed duplicate sig
2020-07-10 3D shape paths & render files
    ...I wish I understood KiCAD better to make these paths stick...
    two render files generated - for Hackaday page
2020-07-15 updated assy plot
    moved plots and BOM files to OUTPUT folder.
2021-04-26 SBC V2 testboard
    KiCad project with testboard, mates with a QMTECH MAX10 board for FPGA.
    Start of VHDL coding for toplevel (phase 0 - just the basics)
